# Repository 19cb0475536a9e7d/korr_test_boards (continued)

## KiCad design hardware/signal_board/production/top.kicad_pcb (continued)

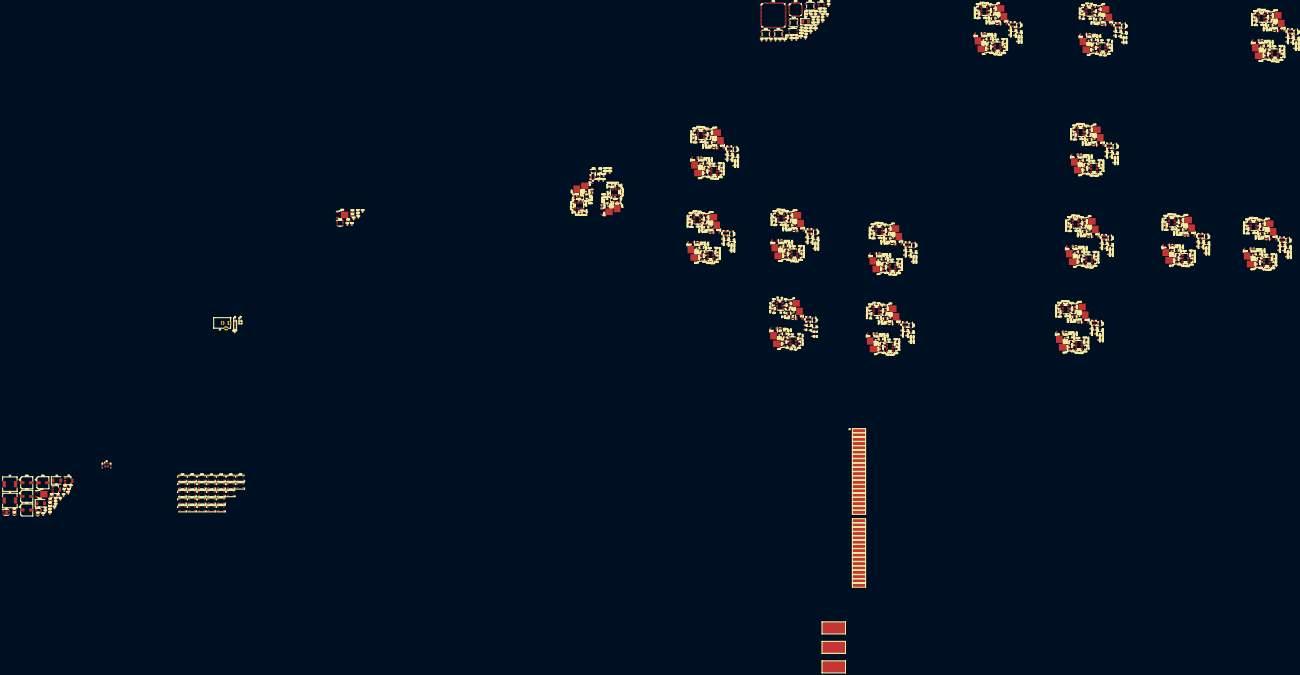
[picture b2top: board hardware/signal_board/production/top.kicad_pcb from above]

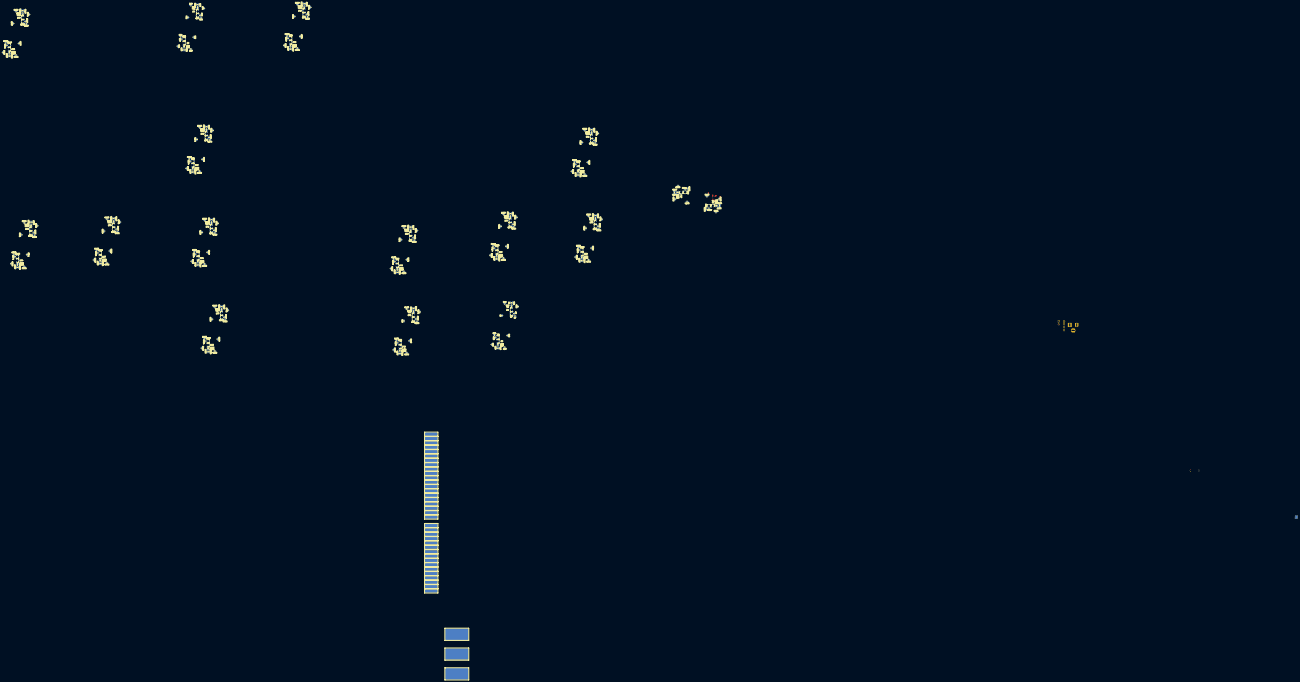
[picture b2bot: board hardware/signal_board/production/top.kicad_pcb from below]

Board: 4 copper layers, 1356 parts (330 on the bottom side), 850 nets.

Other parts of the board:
D7, D8, D9, D10, D15, D16, D17, D18, D19, D20, D21, D22, D23, D24, D25, D26, D27, D28, D29, D30, D31, D32, D33, D34, D35, D36, D37, D38, D39, D40: WS2812B; LED_WS2812B_PLCC4_5.0x5.0mm_P3.2mm

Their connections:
/VCC5V: D7.1, D8.1, D9.1, D10.1, D15.1, D16.1, D17.1, D18.1, D19.1, D20.1, D21.1, D22.1, D23.1, D24.1, D25.1, D26.1, D27.1, D28.1, D29.1, D30.1, D31.1, D32.1, D33.1, D34.1, D35.1, D36.1, D37.1, D38.1, D39.1, D40.1; also elsewhere on the board
/WS2812B_DIN: D7.4; also elsewhere on the board
GNDA: D7.3, D8.3, D9.3, D10.3, D15.3, D16.3, D17.3, D18.3, D19.3, D20.3, D21.3, D22.3, D23.3, D24.3, D25.3, D26.3, D27.3, D28.3, D29.3, D30.3, D31.3, D32.3, D33.3, D34.3, D35.3, D36.3, D37.3, D38.3, D39.3, D40.3; also elsewhere on the board
unnamed: D7.2, D8.4
unnamed: D8.2, D9.4
unnamed: D10.2, D23.4
unnamed: D9.2, D10.4
unnamed: D15.2, D16.4
unnamed: D15.4, D17.2
unnamed: D16.2, D18.4
unnamed: D17.4, D19.2
unnamed: D18.2, D20.4
unnamed: D19.4, D21.2
unnamed: D20.2, D22.4
unnamed: D21.4, D24.2
unnamed: D22.2, D25.4
unnamed: D23.2, D26.4
unnamed: D24.4, D27.2
unnamed: D25.2, D28.4
unnamed: D26.2, D29.4
unnamed: D27.4, D30.2
unnamed: D28.2, D31.4
unnamed: D29.2, D32.4
unnamed: D30.4, D33.2
unnamed: D31.2, D34.4
unnamed: D32.2, D35.4
unnamed: D33.4, D36.2
unnamed: D34.2, D37.4
unnamed: D35.2, D38.4
unnamed: D36.4, D39.2
unnamed: D37.2, D40.4
unnamed: D38.2, D39.4

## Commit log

2020-02-26 initial
2020-02-26 fix B\
    B
    C
    C
    C
2020-02-27 Add priduction board
2020-02-27 Fix .gitmodules
2020-03-02 Add uClibc++
